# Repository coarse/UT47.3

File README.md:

# UT47.3
STM32 40% Keyboard PCB

Keyboard Layout Editor layout: [Layout](http://www.keyboard-layout-editor.com/#/gists/ddc8fda154c2c93ac26e38cd5da5988e)

Made with permission from [KeyHive](https://keyhive.xyz/).

The design is inspired by 40percent.club's Gnap keyboard, which is licensed under [CC BY-SA 4.0](https://creativecommons.org/licenses/by-sa/4.0/).

## Notes

At the moment, UT 47.3 is not compatible with most UT47.2 and UT47 cases. A number of differences from the two other PCBs are as follow:

1. USB port location
  - UT47.3's USB port is located at the top left part of the case. UT47 and UT47.2's USB port is located at the top right part of the case. This will be fixed in another revision
  
2. ARM Microcontroller
  - Unlike UT47 and UT47.2, UT47.3 uses an ARM microcontroller instead of an AVR microcontroller. Specifically, the UT47.3 uses an STM32F072 microcontroller due to not needing an external crystal to use it as an HID keyboard device which keeps costs low.
  
2. Reset switch location/s
  - UT47.3, powered by an STM32 chip, needs two physical switches for reset and entering DFU. Because of that, the location of the switches on the UT47.3 are differnet.
  
3. RGB underglow LED
  - UT47.3 was meant to be a budget PCB therefore the number of underglow LEDs were reduced to 8.
  
4. Single color backlight
  - UT47.3 introduces a simple single-zone backlighting.

5. Non-hotswap
  - Because backlighting is present, using hotswap modules is not an option for this PCB.

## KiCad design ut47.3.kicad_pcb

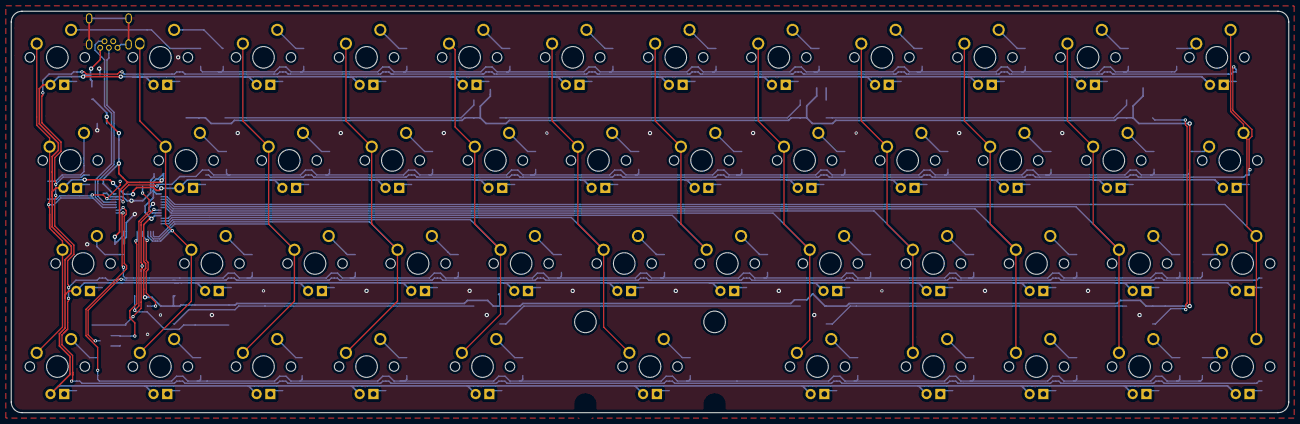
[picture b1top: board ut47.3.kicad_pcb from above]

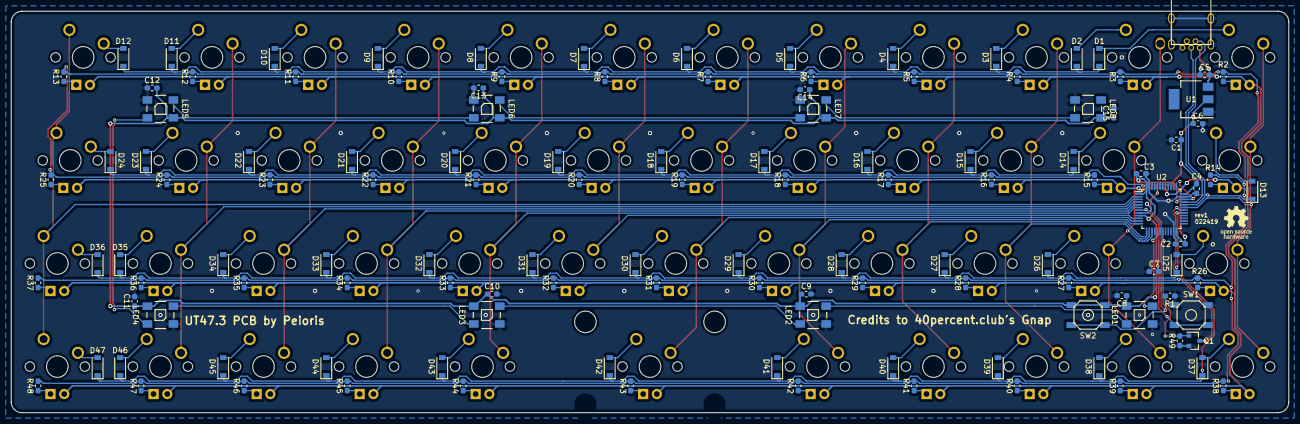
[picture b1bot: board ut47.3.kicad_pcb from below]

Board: 2 copper layers, 236.1 x 74.2 mm, 172 parts (125 on the bottom side), 127 nets.

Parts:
C1, C8, C10, C12: 4.7uF; C_0603_1608Metric_Pad1.05x0.95mm_HandSolder
C2, C3, C4, C7, C9, C11, C13, C14, C15: 100nF; C_0603_1608Metric_Pad1.05x0.95mm_HandSolder
C5, C6: 10uF; C_0603_1608Metric_Pad1.05x0.95mm_HandSolder
D1, D2, D3, D4, D5, D6, D7, D8, D9, D10, D11, D12, D13, D14, D15, D16, D17, D18, D19, D20, D21, D22, D23, D24, D25, D26, D27, D28, D29, D30, D31, D32, D33, D34, D35, D36, D37, D38, D39, D40, D41, D42, D43, D44, D45, D46, D47: D; D_SOD-123
LED1, LED2, LED3, LED4, LED5, LED6, LED7, LED8: WS2812B
MX1, MX2, MX3, MX4, MX5, MX6, MX7, MX8, MX9, MX10, MX11, MX14, MX15, MX16, MX17, MX18, MX19, MX20, MX21, MX22, MX23, MX26, MX27, MX28, MX29, MX30, MX31, MX32, MX33, MX34, MX35, MX36, MX37, MX38, MX39, MX40, MX44, MX45, MX46, MX47: MX-1U; MXOnly-1U
MX12, MX25: MX-1.5U; MXOnly-1.5U
MX13, MX24, MX41, MX43: MX-1.25U; MXOnly-1.25U
MX42: MX-2U; MXOnly-2U-ReversedStabilizers
Q1: MMBT3904; SOT-23
R1, R49: 10k; R_0603_1608Metric_Pad1.05x0.95mm_HandSolder
R2, R3, R4, R5, R6, R7, R8, R9, R10, R11, R12, R13, R14, R15, R16, R17, R18, R19, R20, R21, R22, R23, R24, R25, R26, R27, R28, R29, R30, R31, R32, R33, R34, R35, R36, R37, R38, R39, R40, R41, R42, R43, R44, R45, R46, R47, R48: 470; R_0603_1608Metric_Pad1.05x0.95mm_HandSolder
SW1, SW2: K2-1187SQ-A4SW-06
U1: LD1117AG-33-AA3-A-R; SOT-223
U2: STM32F072CBTx; LQFP-48_7x7mm_P0.5mm
USB1: USB_mini_micro_B; USB-Mini-B_ LCSC-C46398

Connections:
+3V3: C1.1, C2.1, C3.1, C4.1, C6.1, C8.1, C9.1, C10.1, C11.1, C12.1, C13.1, C14.1, C15.1, LED1.1, LED2.1, LED3.1, LED4.1, LED5.1, LED6.1, LED7.1, LED8.1, SW2.2, U1.2, U2.1, U2.9, U2.24, U2.36, U2.48
+5V: C5.2, MX1.3, MX2.3, MX3.3, MX4.3, MX5.3, MX6.3, MX7.3, MX8.3, MX9.3, MX10.3, MX11.3, MX12.3, MX13.3, MX14.3, MX15.3, MX16.3, MX17.3, MX18.3, MX19.3, MX20.3, MX21.3, MX22.3, MX23.3, MX24.3, MX25.3, MX26.3, MX27.3, MX28.3, MX29.3, MX30.3, MX31.3, MX32.3, MX33.3, MX34.3, MX35.3, MX36.3, MX37.3, MX38.3, MX39.3, MX40.3, MX41.3, MX42.3, MX43.3, MX44.3, MX45.3, MX46.3, MX47.3, U1.3, USB1.1
D+: U2.33, USB1.3
D-: U2.32, USB1.2
GND: C1.2, C2.2, C3.2, C4.2, C5.1, C6.2, C7.1, C8.2, C9.2, C10.2, C11.2, C12.2, C13.2, C14.2, C15.2, LED1.3, LED2.3, LED3.3, LED4.3, LED5.3, LED6.3, LED7.3, LED8.3, Q1.2, R1.1, R49.2, SW1.1, U1.1, U2.8, U2.23, U2.35, U2.47, USB1.5, USB1.6
LED: Q1.1, R49.1, U2.19
LEDGND: Q1.3, R2.2, R3.2, R4.2, R5.2, R6.2, R7.2, R8.2, R9.2, R10.2, R11.2, R12.2, R13.2, R14.2, R15.2, R16.2, R17.2, R18.2, R19.2, R20.2, R21.2, R22.2, R23.2, R24.2, R25.2, R26.2, R27.2, R28.2, R29.2, R30.2, R31.2, R32.2, R33.2, R34.2, R35.2, R36.2, R37.2, R38.2, R39.2, R40.2, R41.2, R42.2, R43.2, R44.2, R45.2, R46.2, R47.2, R48.2
unnamed: C7.2, SW1.2, U2.7
unnamed: D1.2, MX1.2
unnamed: D2.2, MX2.2
unnamed: D3.2, MX3.2
unnamed: D4.2, MX4.2
unnamed: D5.2, MX5.2
unnamed: D6.2, MX6.2
unnamed: D7.2, MX7.2
unnamed: D8.2, MX8.2
unnamed: D9.2, MX9.2
unnamed: D10.2, MX10.2
unnamed: D11.2, MX11.2
unnamed: D12.2, MX12.1
unnamed: D13.2, MX13.2
unnamed: D14.2, MX14.2
unnamed: D15.2, MX15.2
unnamed: D16.2, MX16.2
unnamed: D17.2, MX17.2
unnamed: D18.2, MX18.2
unnamed: D19.2, MX19.2
unnamed: D20.2, MX20.2
unnamed: D21.2, MX21.2
unnamed: D22.2, MX22.2
unnamed: D23.2, MX23.2
unnamed: D24.2, MX24.1
unnamed: D25.2, MX25.2
unnamed: D26.2, MX26.2
unnamed: D27.2, MX27.2
unnamed: D28.2, MX28.2
unnamed: D29.2, MX29.2
unnamed: D30.2, MX30.2
unnamed: D31.2, MX31.2
unnamed: D32.2, MX32.2
unnamed: D33.2, MX33.2
unnamed: D34.2, MX34.2
unnamed: D35.2, MX35.2
unnamed: D36.2, MX36.1
unnamed: D37.2, MX37.2
unnamed: D38.2, MX38.2
unnamed: D39.2, MX39.2
unnamed: D40.2, MX40.2
unnamed: D41.2, MX41.2
unnamed: D42.2, MX42.2
unnamed: D43.2, MX43.2
unnamed: D44.2, MX44.2
unnamed: D45.2, MX45.2
unnamed: D46.2, MX46.2
unnamed: D47.2, MX47.1
unnamed: LED1.2, LED2.4
unnamed: LED2.2, LED3.4
unnamed: LED3.2, LED4.4
unnamed: LED4.2, LED5.4
unnamed: LED5.2, LED6.4
unnamed: LED6.2, LED7.4
unnamed: LED7.2, LED8.4
unnamed: MX1.4, R2.1
unnamed: MX2.4, R3.1
unnamed: MX3.4, R4.1
unnamed: MX4.4, R5.1
unnamed: MX5.4, R6.1
unnamed: MX6.4, R7.1
unnamed: MX7.4, R8.1
unnamed: MX8.4, R9.1
unnamed: MX9.4, R10.1
unnamed: MX10.4, R11.1
unnamed: MX11.4, R12.1
unnamed: MX12.4, R13.1
unnamed: MX13.4, R14.1
unnamed: MX14.4, R15.1
unnamed: MX15.4, R16.1
unnamed: MX16.4, R17.1
unnamed: MX17.4, R18.1
unnamed: MX18.4, R19.1
unnamed: MX19.4, R20.1
unnamed: MX20.4, R21.1
unnamed: MX21.4, R22.1
unnamed: MX22.4, R23.1
unnamed: MX23.4, R24.1
unnamed: MX24.4, R25.1
unnamed: MX25.4, R26.1
unnamed: MX26.4, R27.1
unnamed: MX27.4, R28.1
unnamed: MX28.4, R29.1
unnamed: MX29.4, R30.1
unnamed: MX30.4, R31.1
unnamed: MX31.4, R32.1
unnamed: MX32.4, R33.1
unnamed: MX33.4, R34.1
unnamed: MX34.4, R35.1
unnamed: MX35.4, R36.1
unnamed: MX36.4, R37.1
unnamed: MX37.4, R38.1
unnamed: MX38.4, R39.1
unnamed: MX39.4, R40.1
unnamed: MX40.4, R41.1
unnamed: MX41.4, R42.1
unnamed: MX42.4, R43.1
unnamed: MX43.4, R44.1
unnamed: MX44.4, R45.1
unnamed: MX45.4, R46.1
unnamed: MX46.4, R47.1
unnamed: MX47.4, R48.1
unnamed: R1.2, SW2.1, U2.44
colA: MX1.1, MX13.1, MX25.1, MX37.1, U2.31
colB: MX2.1, MX14.1, MX26.1, MX38.1, U2.15
colC: MX3.1, MX15.1, MX27.1, MX39.1, U2.14
colD: MX4.1, MX16.1, MX28.1, MX40.1, U2.13
colE: MX5.1, MX17.1, MX29.1, MX41.1, U2.12
colF: MX6.1, MX18.1, MX30.1, MX42.1, U2.11
colG: MX7.1, MX19.1, MX31.1, U2.10
colH: MX8.1, MX20.1, MX32.1, MX43.1, U2.6
colI: MX9.1, MX21.1, MX33.1, MX44.1, U2.5
colJ: MX10.1, MX22.1, MX34.1, MX45.1, U2.4
colK: MX11.1, MX23.1, MX35.1, MX46.1, U2.3
colL: MX12.2, MX24.2, MX36.2, MX47.2, U2.2
row0: D1.1, D2.1, D3.1, D4.1, D5.1, D6.1, D7.1, D8.1, D9.1, D10.1, D11.1, D12.1
row1: D13.1, D14.1, D15.1, D16.1, D17.1, D18.1, D19.1, D20.1, D21.1, D22.1, D23.1, D24.1, U2.34
row2: D25.1, D26.1, D27.1, D28.1, D29.1, D30.1, D31.1, D32.1, D33.1, D34.1, D35.1, D36.1, U2.29
row3: D37.1, D38.1, D39.1, D40.1, D41.1, D42.1, D43.1, D44.1, D45.1, D46.1, D47.1, U2.30
ws2812: LED1.4, U2.17

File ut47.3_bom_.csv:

Component,Description,Part,References,Value,Footprint,Quantity Per PCB,Datasheet
1,,C,C2 C3 C4 C7 C9 C11 C13 C14 C15,100nF,C_0603_1608Metric_Pad1.05x0.95mm_HandSolder,9,
2,,C,C5 C6,10uF,C_0603_1608Metric_Pad1.05x0.95mm_HandSolder,2,
3,,C,C1 C8 C10 C12,4.7uF,C_0603_1608Metric_Pad1.05x0.95mm_HandSolder,4,
4,,D,D1 D2 D3 D4 D5 D6 D7 D8 D9 D10 D11 D12 D13 D14 D15 D16 D17 D18 D19 D20 D21 D22 D23 D24 D25 D26 D27 D28 D29 D30 D31 D32 D33 D34 D35 D36 D37 D38 D39 D40 D41 D42 D43 D44 D45 D46 D47,D,D_SOD-123,47,
5,RGB LED with integrated controller,WS2812B,LED1 LED2 LED3 LED4 LED5 LED6 LED7 LED8,WS2812B,WS2812B,8,
6,,MX-1.25U,MX13 MX24 MX41 MX43,MX-1.25U,MXOnly-1.25U,4,
7,,MX-1.5U,MX12 MX25,MX-1.5U,MXOnly-1.5U,2,
8,,MX-1U,MX1 MX2 MX3 MX4 MX5 MX6 MX7 MX8 MX9 MX10 MX11 MX14 MX15 MX16 MX17 MX18 MX19 MX20 MX21 MX22 MX23 MX26 MX27 MX28 MX29 MX30 MX31 MX32 MX33 MX34 MX35 MX36 MX37 MX38 MX39 MX40 MX44 MX45 MX46 MX47,MX-1U,MXOnly-1U,40,
9,,MX-2U,MX42,MX-2U,MXOnly-2U-ReversedStabilizers,1,
10,"0.2A Ic, 40V Vce, Small Signal NPN Transistor, SOT-23",MMBT3904,Q1,MMBT3904,SOT-23,1,https://www.fairchildsemi.com/datasheets/2N/2N3904.pdf
11,,R,R1 R49,10k,R_0603_1608Metric_Pad1.05x0.95mm_HandSolder,2,
12,,R,R2 R3 R4 R5 R6 R7 R8 R9 R10 R11 R12 R13 R14 R15 R16 R17 R18 R19 R20 R21 R22 R23 R24 R25 R26 R27 R28 R29 R30 R31 R32 R33 R34 R35 R36 R37 R38 R39 R40 R41 R42 R43 R44 R45 R46 R47 R48,470,R_0603_1608Metric_Pad1.05x0.95mm_HandSolder,47,
13,,SW,SW1 SW2,K2-1187SQ-A4SW-06,K2-1187SQ-A4SW-06,2,
14,,LDO_REG,U1,LD1117AG-33-AA3-A-R,SOT-223,1,
15,"ARM Cortex-M0 MCU, 128KB flash, 16KB RAM, 48MHz, 2-3.6V, 37 GPIO, LQFP-48",STM32F072CBTx,U2,STM32F072CBTx,LQFP-48_7x7mm_P0.5mm,1,http://www.st.com/st-web-ui/static/active/en/resource/techni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
16,,USB_mini_micro_B,USB1,USB_mini_micro_B,USB-Mini-B_ LCSC-C46398,1,





Component Groups:,16
Component Count:,172
Fitted Components:,172
Number of PCBs:,1
Total components:,172
Schematic Version:,
Schematic Date:,
BoM Date:,2/24/2019 9:29:57 PM
Schematic Source:,E:\Desktop\Peioris Boards\keyboard works\UT47.3\ut47.3.sch
KiCad Version:,Eeschema (5.0.1)-4

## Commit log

2019-02-24 inital commit
2019-02-24 add license
2019-02-24 add bom files

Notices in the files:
README.md:
Creative Commons Attribution-ShareAlike 4.0 International License
